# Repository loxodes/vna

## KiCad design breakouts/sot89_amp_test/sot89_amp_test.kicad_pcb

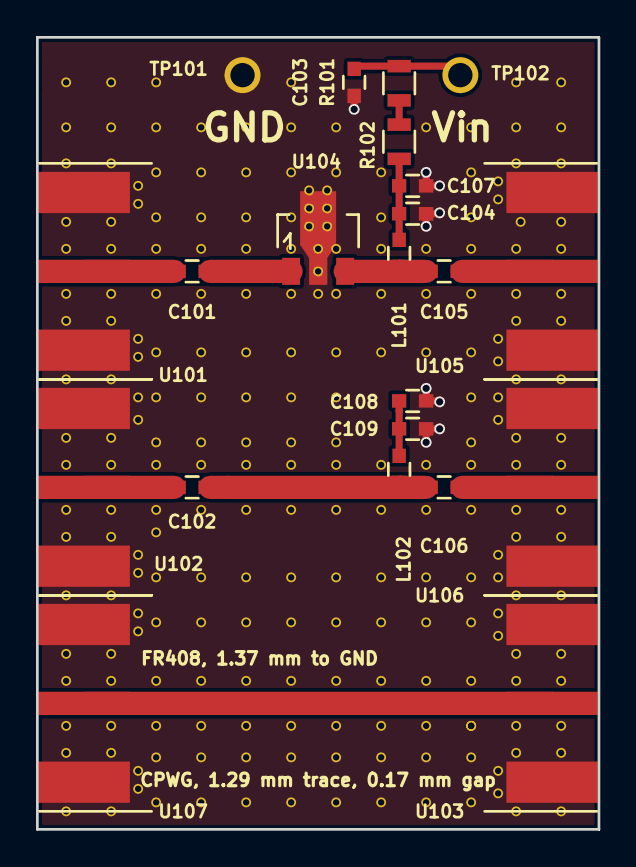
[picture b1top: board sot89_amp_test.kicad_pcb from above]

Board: 4 copper layers, 31.2 x 44.0 mm, 22 parts (0 on the bottom side), 13 nets.

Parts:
C101, C102, C103, C104, C105, C106, C107, C108, C109: C_Small; C_0603
L101, L102: BLM18GG471SN1; C_0603
R101, R102: R_Small; R_0805
TP101, TP102: TEST; TURRET_MILLMAX_2101
U101, U102, U103, U105, U106, U107: CONN_SMA; 732511150_sma_thin
U104: SKY65013-70LF; SOT89-3_Housing

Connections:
GND: C103.2, C104.2, C107.2, C108.2, C109.2, TP101.1, U101.2, U101.3, U101.4, U101.5, U102.2, U102.3, U102.4, U102.5, U103.2, U103.3, U103.4, U103.5, U104.2, U105.2, U105.3, U105.4, U105.5, U106.2, U106.3, U106.4, U106.5, U107.2, U107.3, U107.4, U107.5
unnamed: C101.1, U104.1
unnamed: C101.2, U101.1
unnamed: C102.1, C106.2, L102.1
unnamed: C102.2, U102.1
unnamed: C103.1, R101.1, TP102.1
unnamed: C104.1, C107.1, L101.2, R102.2
unnamed: C105.1, U105.1
unnamed: C105.2, L101.1, U104.3
unnamed: C106.1, U106.1
unnamed: C108.1, C109.1, L102.2
unnamed: R101.2, R102.1
unnamed: U103.1, U107.1

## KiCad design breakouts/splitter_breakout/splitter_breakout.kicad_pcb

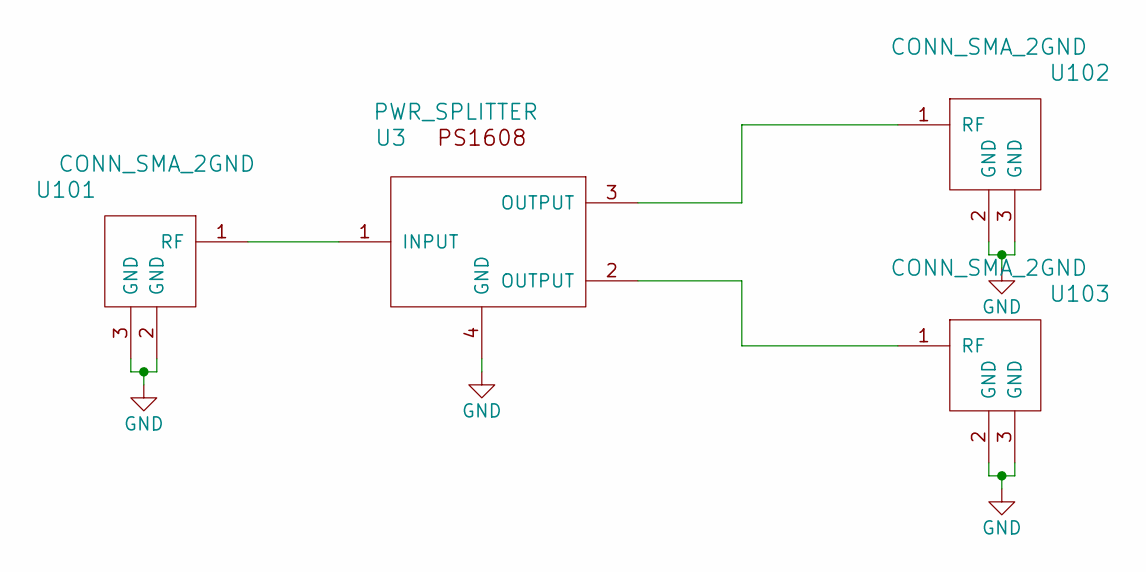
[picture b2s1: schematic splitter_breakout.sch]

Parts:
U3: PWR_SPLITTER; PS1608
U101, U102, U103: CONN_SMA_2GND; SMA_CPW_1MM_.2MM

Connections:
GND: U3.4 (GND), U101.2 (GND), U101.3 (GND), U102.2 (GND), U102.3 (GND), U103.2 (GND), U103.3 (GND)
unnamed: U3.1 (INPUT), U101.1 (RF)
unnamed: U3.3 (OUTPUT), U102.1 (RF)
unnamed: U3.2 (OUTPUT), U103.1 (RF)

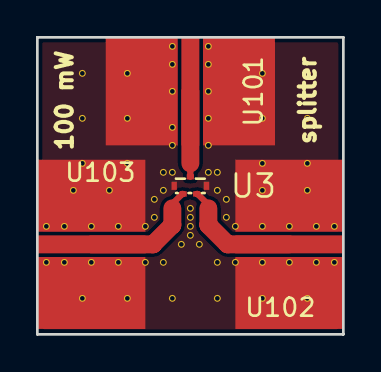
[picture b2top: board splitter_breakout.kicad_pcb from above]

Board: 4 copper layers, 17.0 x 16.5 mm, 4 parts (0 on the bottom side), 4 nets.

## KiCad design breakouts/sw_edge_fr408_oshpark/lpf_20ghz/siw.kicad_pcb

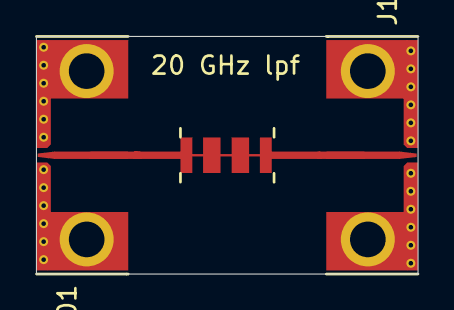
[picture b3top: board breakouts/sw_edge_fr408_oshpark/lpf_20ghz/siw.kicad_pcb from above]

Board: 4 copper layers, 21.2 x 13.2 mm, 3 parts (0 on the bottom side), 3 nets.

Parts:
FL101: low_pass_filter; stepped_lpf_20ghz_fr408
J101, J102: Conn_Coaxial; sw_edge_oshpark_4layer

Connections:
GND: J101.2, J102.2
unnamed: FL101.1, J101.1
unnamed: FL101.2, J102.1

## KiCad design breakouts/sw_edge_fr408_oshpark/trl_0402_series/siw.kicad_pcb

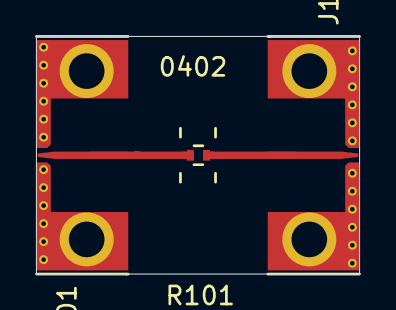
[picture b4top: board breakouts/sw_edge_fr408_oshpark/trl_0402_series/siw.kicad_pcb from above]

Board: 4 copper layers, 17.9 x 13.2 mm, 3 parts (0 on the bottom side), 3 nets.

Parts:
J101, J102: Conn_Coaxial; sw_edge_oshpark_4layer
R101: R_Small; R_0402

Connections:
GND: J101.2, J102.2
unnamed: J101.1, R101.2
unnamed: J102.1, R101.1

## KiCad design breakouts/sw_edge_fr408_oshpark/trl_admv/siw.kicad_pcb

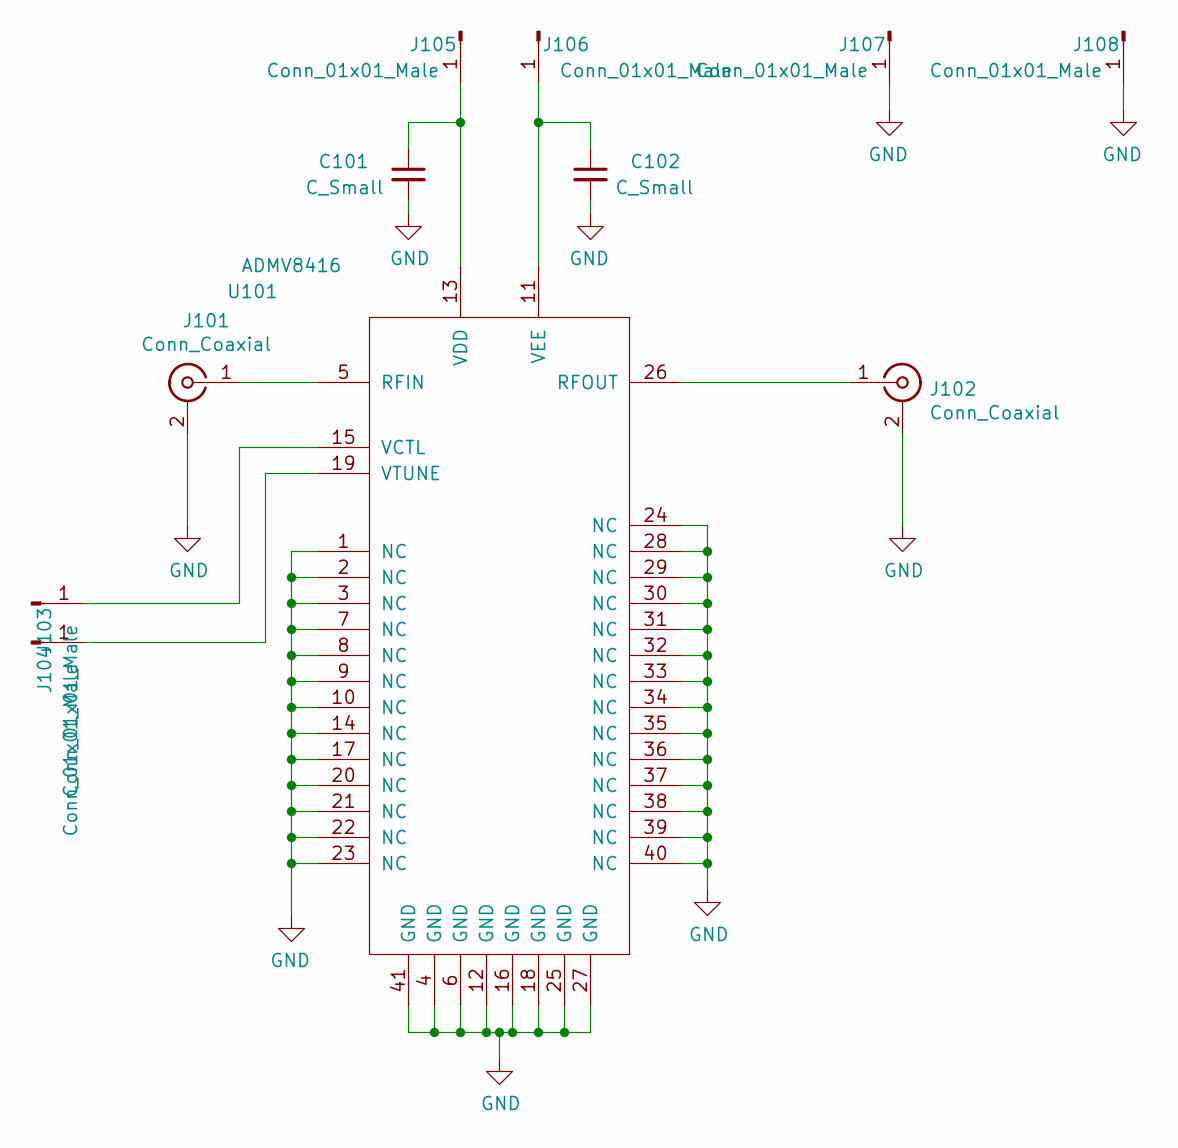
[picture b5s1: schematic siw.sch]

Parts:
C101, C102: C_Small; C_0402
J101, J102: Conn_Coaxial; sw_edge_oshpark_4layer
J103, J104, J105, J106, J107, J108: Conn_01x01_Male; TURRET_MILLMAX_2101
U101: ADMV8416; QFN-40-1EP_6x6mm_Pitch0.5mm

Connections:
GND: C101.2, C102.2, J101.2 (Ext), J102.2 (Ext), J107.1, J108.1, U101.1 (NC), U101.2 (NC), U101.3 (NC), U101.4 (GND), U101.6 (GND), U101.7 (NC), U101.8 (NC), U101.9 (NC), U101.10 (NC), U101.12 (GND), U101.14 (NC), U101.16 (GND), U101.17 (NC), U101.18 (GND), U101.20 (NC), U101.21 (NC), U101.22 (NC), U101.23 (NC), U101.24 (NC), U101.25 (GND), U101.27 (GND), U101.28 (NC), U101.29 (NC), U101.30 (NC), U101.31 (NC), U101.32 (NC), U101.33 (NC), U101.34 (NC), U101.35 (NC), U101.36 (NC), U101.37 (NC), U101.38 (NC), U101.39 (NC), U101.40 (NC), U101.41 (GND)
unnamed: C101.1, J105.1, U101.13 (VDD)
unnamed: C102.1, J106.1, U101.11 (VEE)
unnamed: J101.1 (In), U101.5 (RFIN)
unnamed: J102.1 (In), U101.26 (RFOUT)
unnamed: J103.1, U101.15 (VCTL)
unnamed: J104.1, U101.19 (VTUNE)

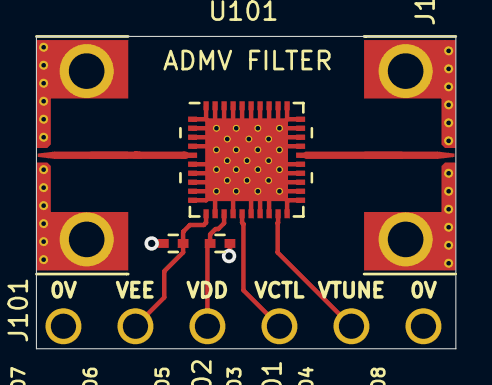
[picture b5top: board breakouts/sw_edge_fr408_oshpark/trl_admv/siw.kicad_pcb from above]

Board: 4 copper layers, 23.3 x 17.3 mm, 11 parts (0 on the bottom side), 7 nets.
